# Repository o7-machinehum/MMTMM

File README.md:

# MMM 
Makers Make Music. We're designing and building 100% open source eurorack modules, we would love to hear [from you](https://docs.google.com/forms/d/e/1FAIpQLSeDmKGT8nFPX62po_9shZNs7qYtOch9zK6xhK_ntmRhs4zbUg/viewform?vc=0&c=0&w=1)! All of our designs are done in kicad, which is an open source PCB design software.

## Drum (Bob Bass)
The [Bob Bass](https://github.com/Machine-Hum/MMTMM/tree/master/DrumModule) takes inspiration from the 808 service manual. This guy has knobs all over the place: HPF, LPF, overdrive and control over the resonance and decay. [AUDIO](https://drive.google.com/file/d/1c2VHwUoPN1qcCgDcaHPTnX8EYp0KqyGa/view?usp=sharing) --- [VIDEO](https://www.youtube.com/watch?v=IFoyo2GT42M)

## Logic Crusher
This is a design that conditions synth level audio into 4bit digital. These signals can then be routed through standard TTL logic and then converted back into audio. It's possible to make some very complex sounds. Here is the faceplate, patching is done through the back of the panel.

Some wavforms, the blue is the input and the yellow is the output. <br>

The current setup... (Will be made into a module later)

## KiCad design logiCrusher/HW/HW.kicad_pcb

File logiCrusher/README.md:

# Hardware
## Notes / TODO
- Light pipes in the BOM are too short
- Audio connectors are incorrect (Fixed but double check)
- SWD lines are not correct (Fixed but double check)

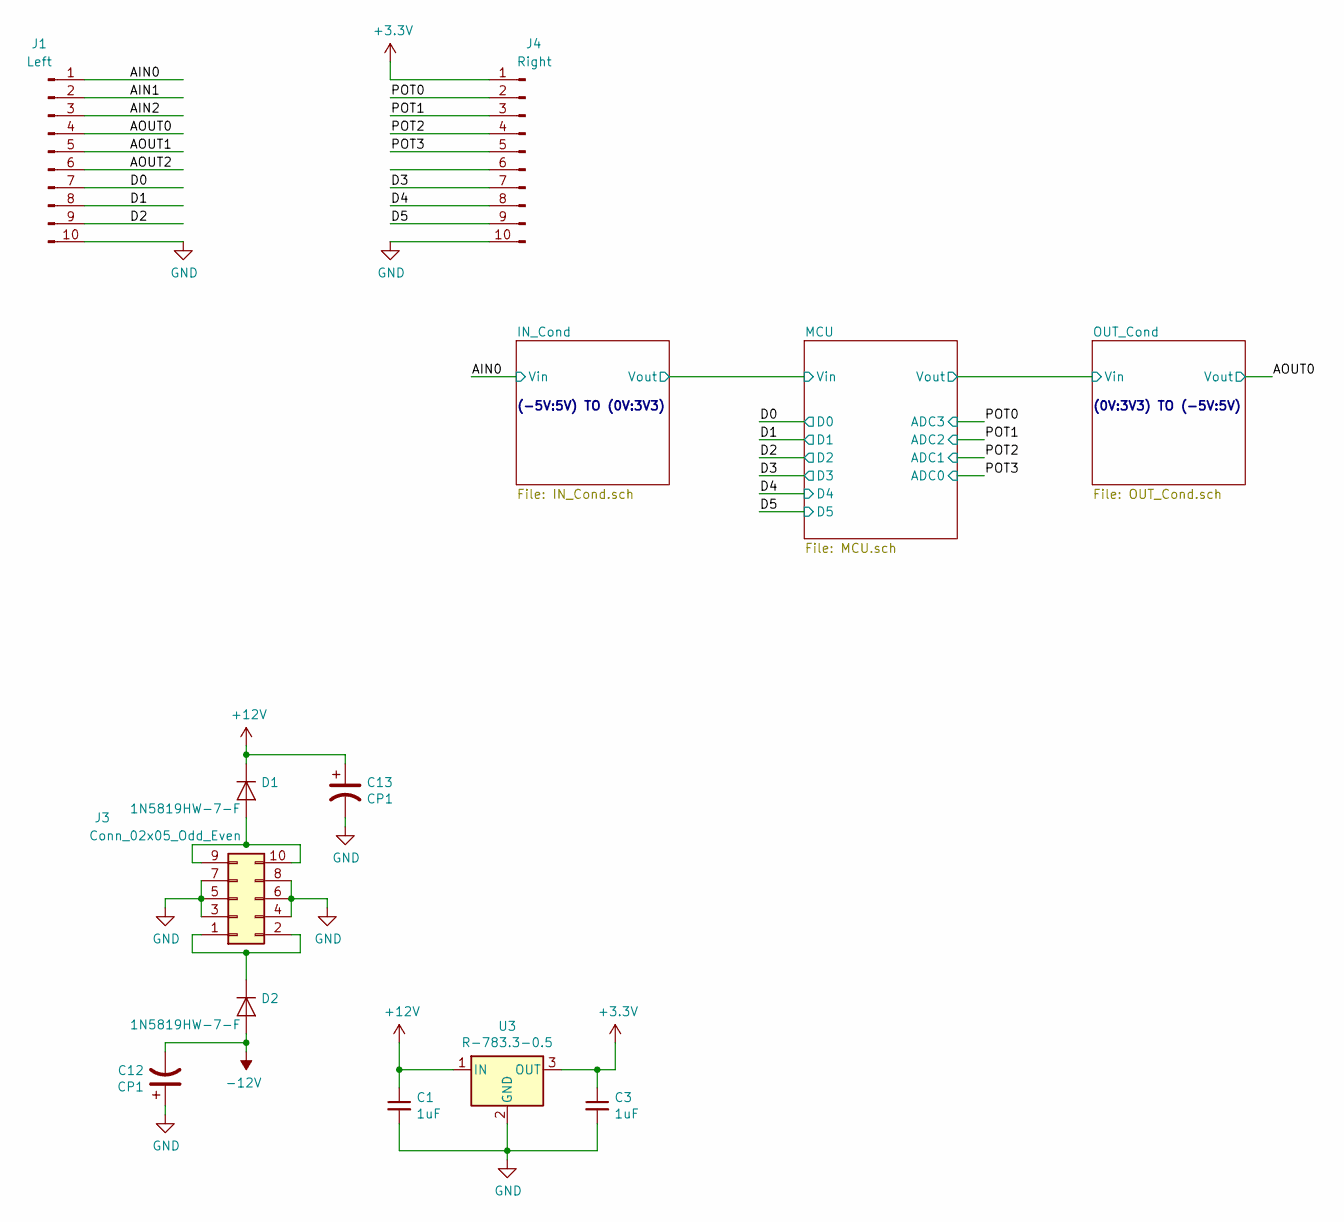
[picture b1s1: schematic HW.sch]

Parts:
C1, C3: 1uF; C_0805_2012Metric
C12, C13: CP1; CP_Elec_3x5.3
D1, D2: 1N5819HW-7-F; D_SOD-123
J1: Left; PinSocket_1x10_P2.54mm_Vertical
J3: Conn_02x05_Odd_Even; IDC-Header_2x05_P2.54mm_Vertical
J4: Right; PinSocket_1x10_P2.54mm_Vertical
U3: R-783.3-0.5; Converter_DCDC_RECOM_R-78E-0.5_THT

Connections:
+3V3: C3.1, J4.1, U3.3 (OUT); also elsewhere on the board
+12V: C1.1, C13.1, D1.1 (K), U3.1 (IN); also elsewhere on the board
-12V: C12.2, D2.2 (A); also elsewhere on the board
/AIN0: J1.1; also elsewhere on the board
/AIN1: J1.2
/AIN2: J1.3
/AOUT0: J1.4; also elsewhere on the board
/AOUT1: J1.5
/AOUT2: J1.6
/D0: J1.7; also elsewhere on the board
/D1: J1.8; also elsewhere on the board
/D2: J1.9; also elsewhere on the board
/D3: J4.7; also elsewhere on the board
/D4: J4.8; also elsewhere on the board
/D5: J4.9; also elsewhere on the board
/POT0: J4.2; also elsewhere on the board
/POT1: J4.3; also elsewhere on the board
/POT2: J4.4; also elsewhere on the board
/POT3: J4.5; also elsewhere on the board
GND: C1.2, C3.2, C12.1, C13.2, J1.10, J3.3, J3.4, J3.5, J3.6, J3.7, J3.8, J4.10, U3.2 (GND); also elsewhere on the board
unnamed: D1.2 (A), J3.9, J3.10
unnamed: D2.1 (K), J3.1, J3.2

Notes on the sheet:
(-5V:5V) TO (0V:3V3)
(0V:3V3) TO (-5V:5V)

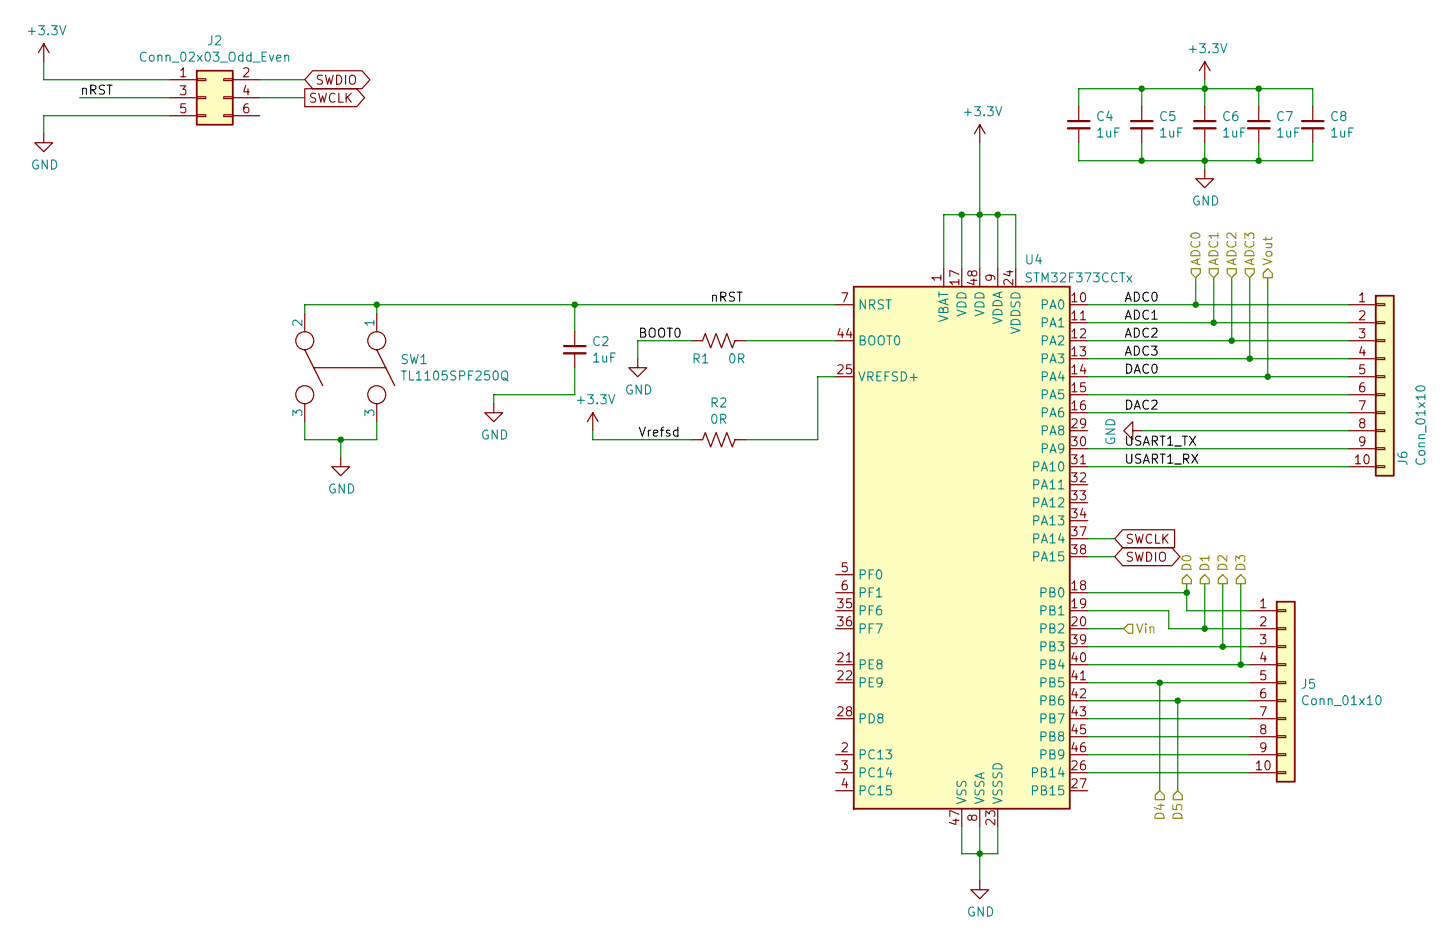
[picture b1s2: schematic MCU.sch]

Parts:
C2, C4, C5, C6, C7, C8: 1uF; C_0805_2012Metric
J2: Conn_02x03_Odd_Even; PinHeader_2x03_P2.54mm_Vertical
J5, J6: Conn_01x10; PinHeader_1x10_P2.54mm_Vertical
R1, R2: 0R; R_0805_2012Metric
SW1: TL1105SPF250Q
U4: STM32F373CCTx; LQFP-48_7x7mm_P0.5mm

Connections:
+3V3: C4.1, C5.1, C6.1, C7.1, C8.1, J2.1, R2.2, U4.1 (VBAT), U4.9 (VDDA), U4.17 (VDD), U4.24 (VDDSD), U4.48 (VDD); also elsewhere on the board
/D0: J5.1, U4.18 (PB0); also elsewhere on the board
/D1: J5.2, U4.19 (PB1); also elsewhere on the board
/D2: J5.3, U4.39 (PB3); also elsewhere on the board
/D3: J5.4, U4.40 (PB4); also elsewhere on the board
/D4: J5.5, U4.41 (PB5); also elsewhere on the board
/D5: J5.6, U4.42 (PB6); also elsewhere on the board
/MCU/DAC2: J6.7, U4.16 (PA6)
/MCU/USART1_RX: J6.10, U4.31 (PA10)
/MCU/USART1_TX: J6.9, U4.30 (PA9)
/MCU/Vin: U4.20 (PB2); also elsewhere on the board
/MCU/nRST: C2.1, J2.3, SW1.1, SW1.2, U4.7 (NRST)
/OUT_Cond/Vin: J6.5, U4.14 (PA4); also elsewhere on the board
/POT0: J6.4, U4.13 (PA3); also elsewhere on the board
/POT1: J6.3, U4.12 (PA2); also elsewhere on the board
/POT2: J6.2, U4.11 (PA1); also elsewhere on the board
/POT3: J6.1, U4.10 (PA0); also elsewhere on the board
GND: C2.2, C4.2, C5.2, C6.2, C7.2, C8.2, J2.5, J6.8, R1.2, SW1.3, U4.8 (VSSA), U4.23 (VSSSD), U4.47 (VSS); also elsewhere on the board
unnamed: J5.7, U4.43 (PB7)
unnamed: J5.8, U4.45 (PB8)
unnamed: J5.9, U4.46 (PB9)
unnamed: J5.10, U4.26 (PB14)
unnamed: J6.6, U4.15 (PA5)
unnamed: R1.1, U4.44 (BOOT0)
unnamed: R2.1, U4.25 (VREFSD+)
SWCLK: J2.4, U4.37 (PA14)
SWDIO: J2.2, U4.38 (PA15)

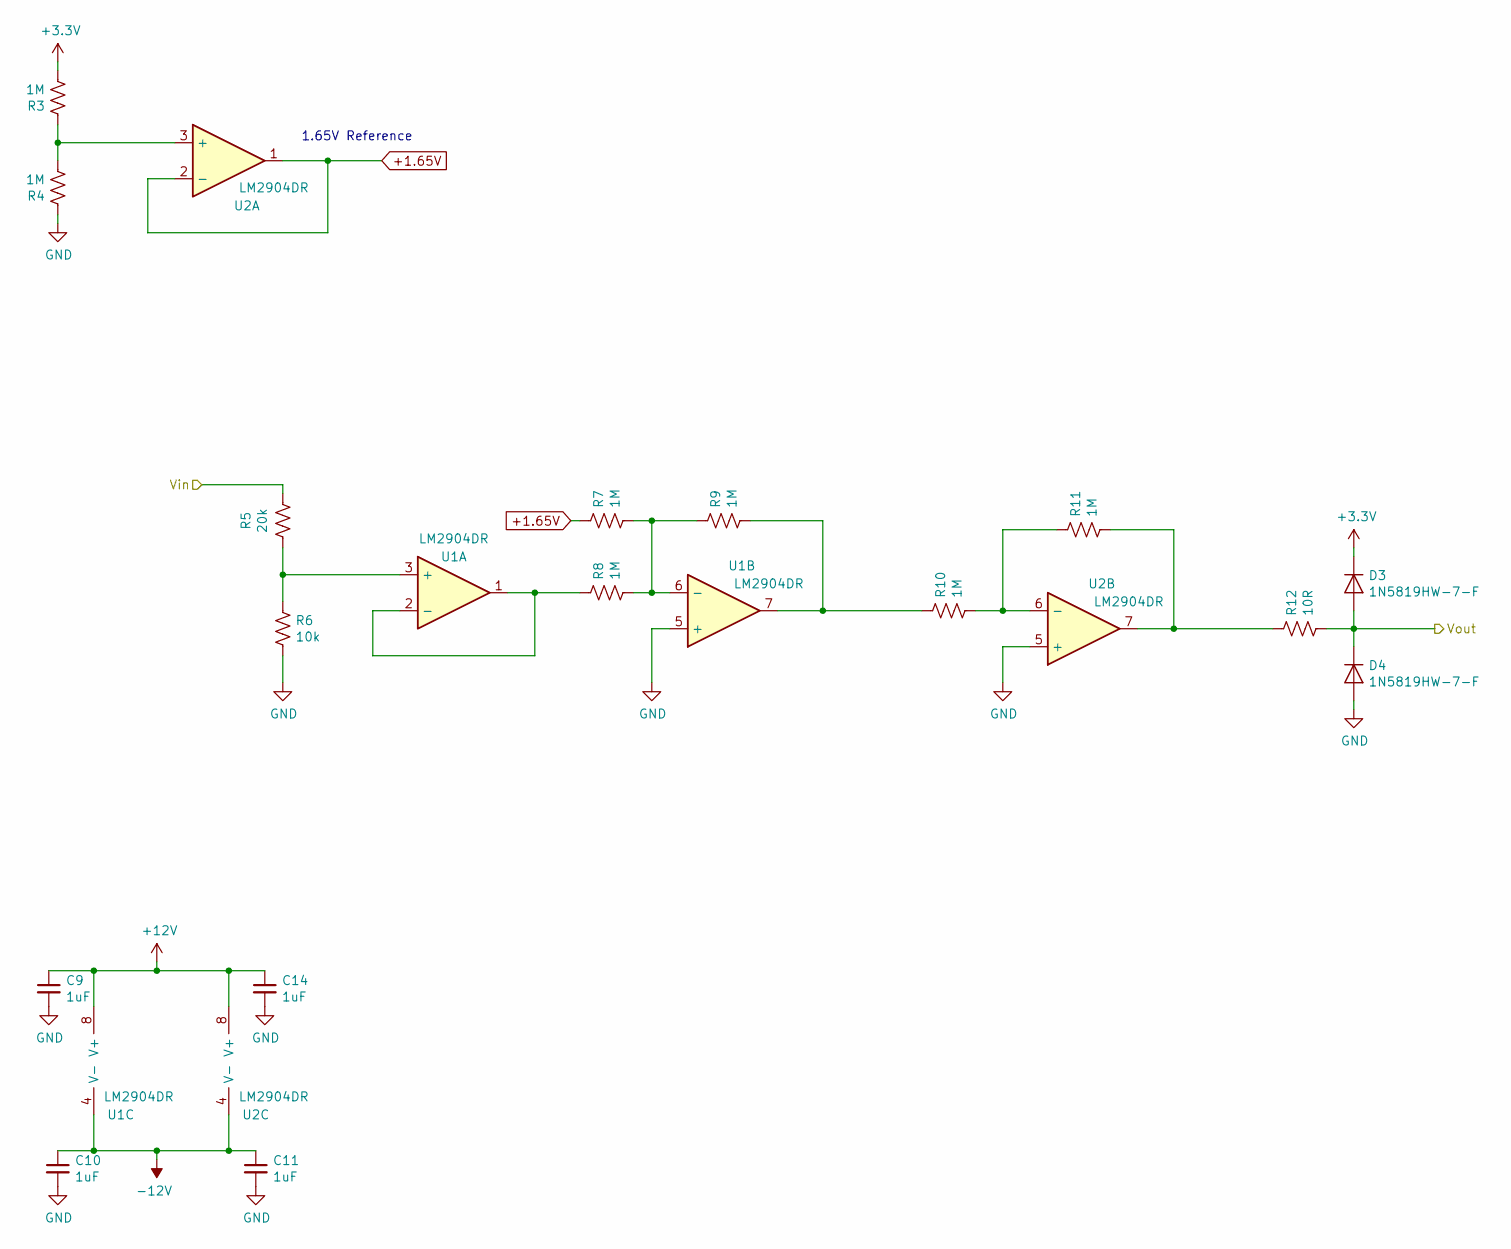
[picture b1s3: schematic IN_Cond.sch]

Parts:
C9, C10, C11, C14: 1uF; C_0805_2012Metric
D3, D4: 1N5819HW-7-F; D_SOD-123
R3, R4, R7, R8, R9, R10, R11: 1M; R_0805_2012Metric
R5: 20k; R_0805_2012Metric
R6: 10k; R_0805_2012Metric
R12: 10R; R_0805_2012Metric
U1, U2: LM2904DR; SOIC-8_3.9x4.9mm_P1.27mm

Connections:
+1.65V: R7.2, U2.1, U2.2 (-); also elsewhere on the board
+3V3: D3.1 (K), R3.1; also elsewhere on the board
+12V: C9.1, C14.1, U1.8 (V+), U2.8 (V+); also elsewhere on the board
-12V: C10.1, C11.1, U1.4 (V-), U2.4 (V-); also elsewhere on the board
/AIN0: R5.1; also elsewhere on the board
/MCU/Vin: D3.2 (A), D4.1 (K), R12.1; also elsewhere on the board
GND: C9.2, C10.2, C11.2, C14.2, D4.2 (A), R4.2, R6.1, U1.5 (+), U2.5 (+); also elsewhere on the board
unnamed: R3.2, R4.1, U2.3 (+)
unnamed: R5.2, R6.2, U1.3 (+)
unnamed: R7.1, R8.1, R9.2, U1.6 (-)
unnamed: R8.2, U1.1, U1.2 (-)
unnamed: R10.1, R11.2, U2.6 (-)
unnamed: R9.1, R10.2, U1.7
unnamed: R11.1, R12.2, U2.7

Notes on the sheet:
1.65V Reference

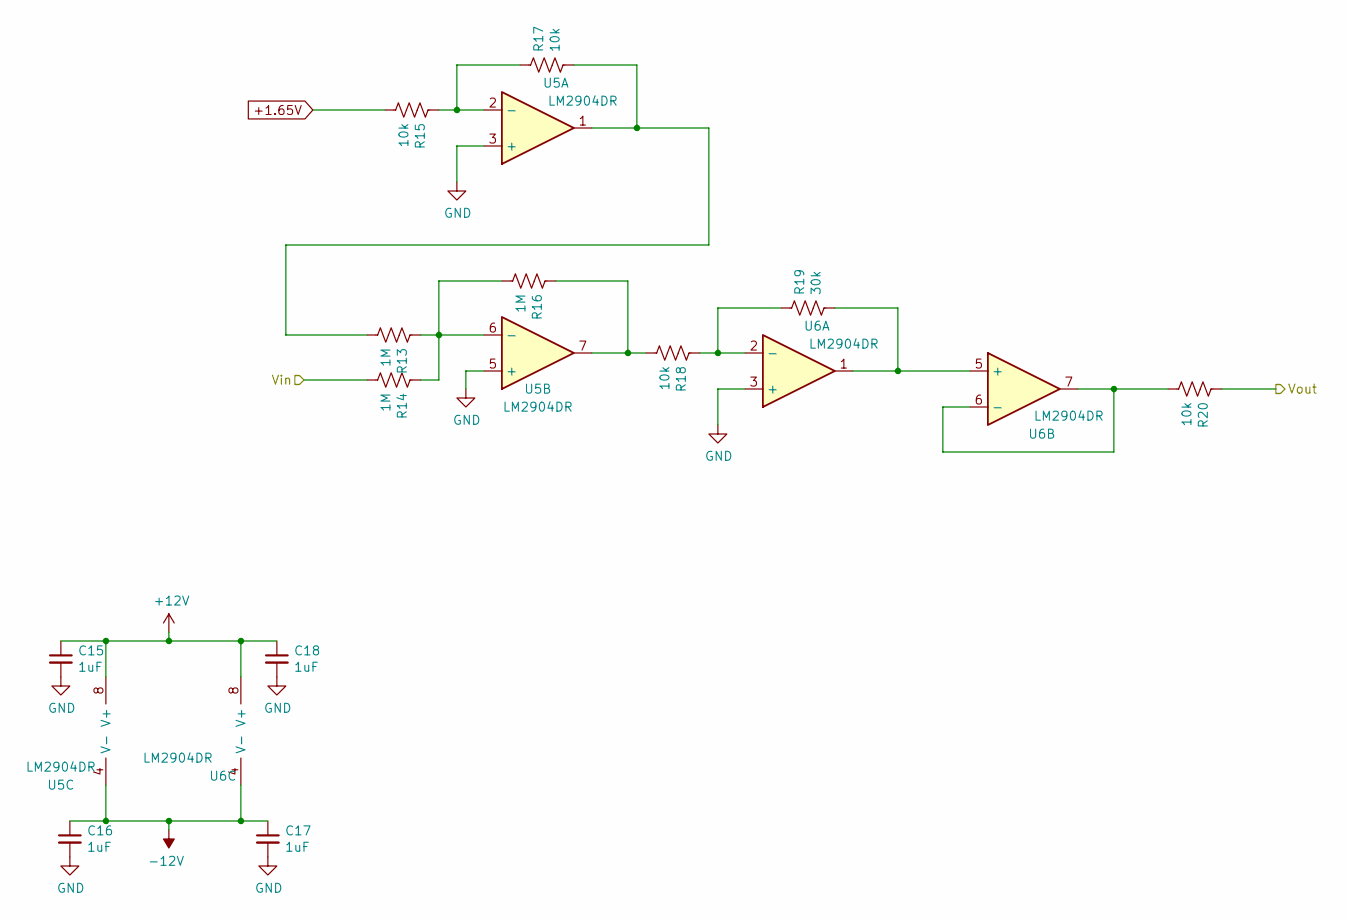
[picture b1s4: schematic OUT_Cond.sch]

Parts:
C15, C16, C17, C18: 1uF; C_0805_2012Metric
R13, R14, R16: 1M; R_0805_2012Metric
R15, R17, R18, R20: 10k; R_0805_2012Metric
R19: 30k; R_0805_2012Metric
U5, U6: LM2904DR; SOIC-8_3.9x4.9mm_P1.27mm

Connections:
+1.65V: R15.1; also elsewhere on the board
+12V: C15.1, C18.1, U5.8 (V+), U6.8 (V+); also elsewhere on the board
-12V: C16.1, C17.1, U5.4 (V-), U6.4 (V-); also elsewhere on the board
/AOUT0: R20.2; also elsewhere on the board
/OUT_Cond/Vin: R14.1; also elsewhere on the board
GND: C15.2, C16.2, C17.2, C18.2, U5.3 (+), U5.5 (+), U6.3 (+); also elsewhere on the board
unnamed: R13.1, R17.1, U5.1
unnamed: R13.2, R14.2, R16.1, U5.6 (-)
unnamed: R15.2, R17.2, U5.2 (-)
unnamed: R16.2, R18.1, U5.7
unnamed: R18.2, R19.2, U6.2 (-)
unnamed: R19.1, U6.1, U6.5 (+)
unnamed: R20.1, U6.6 (-), U6.7

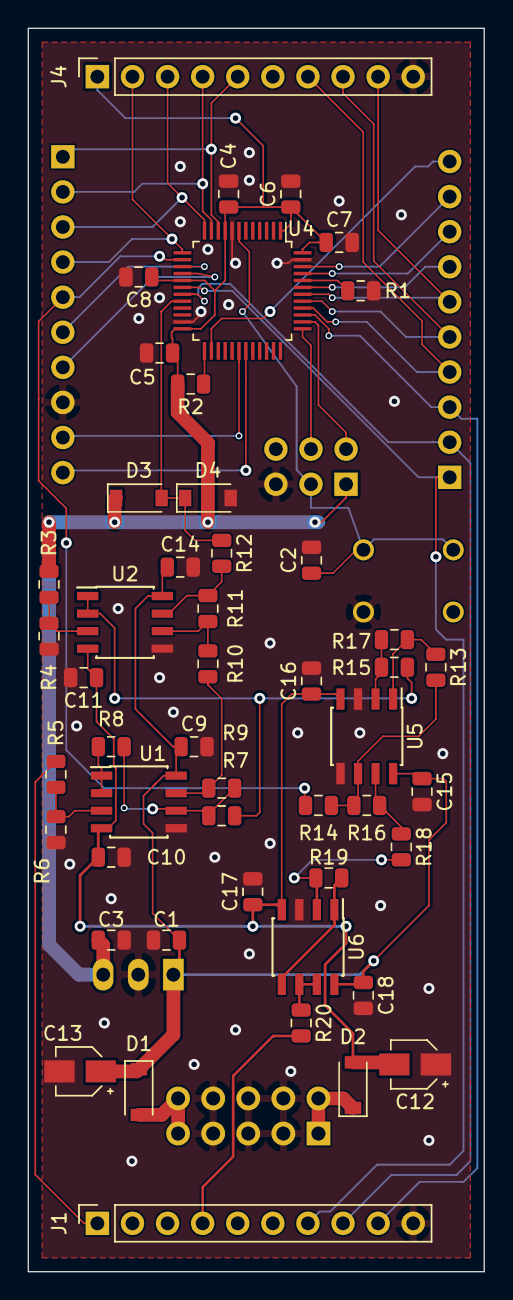
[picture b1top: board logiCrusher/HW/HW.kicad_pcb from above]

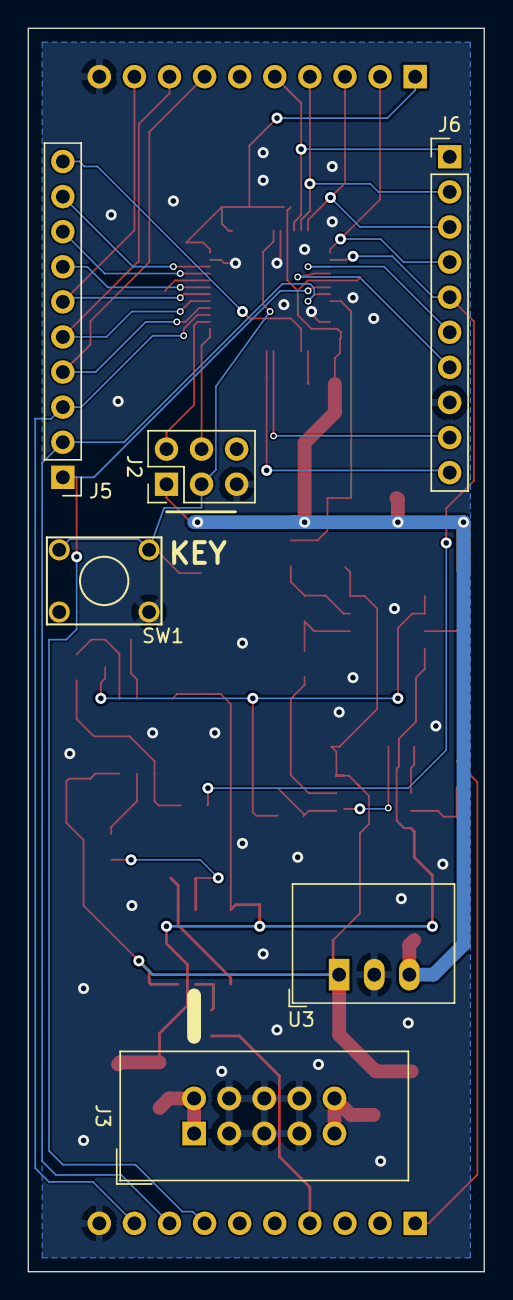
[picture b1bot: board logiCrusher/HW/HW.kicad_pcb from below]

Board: 2 copper layers, 33.0 x 90.0 mm, 55 parts (6 on the bottom side), 48 nets.

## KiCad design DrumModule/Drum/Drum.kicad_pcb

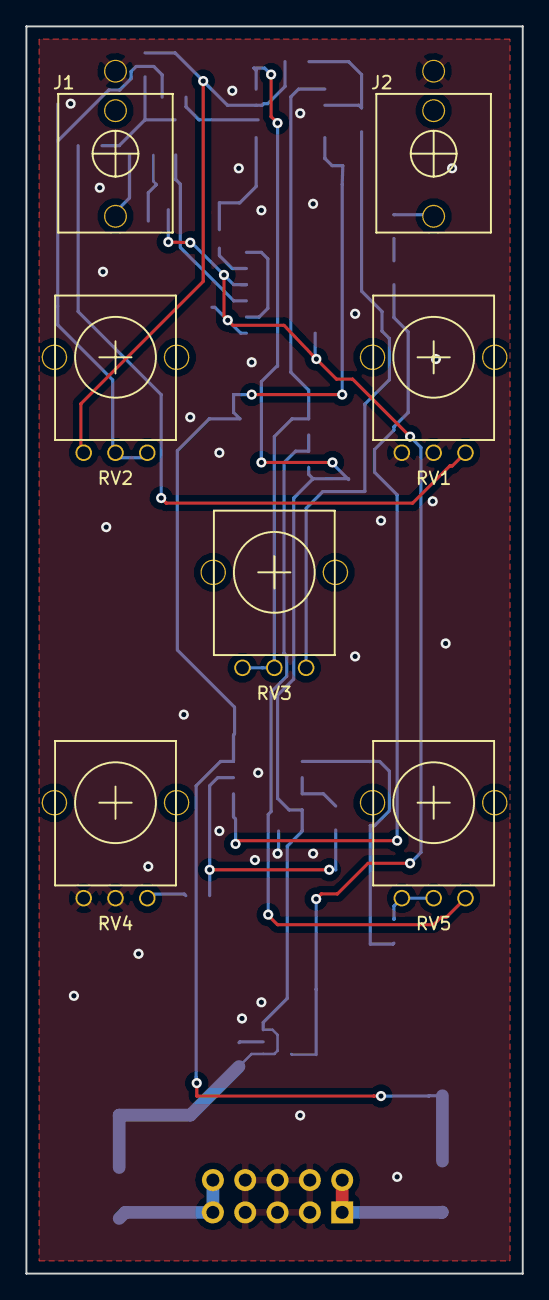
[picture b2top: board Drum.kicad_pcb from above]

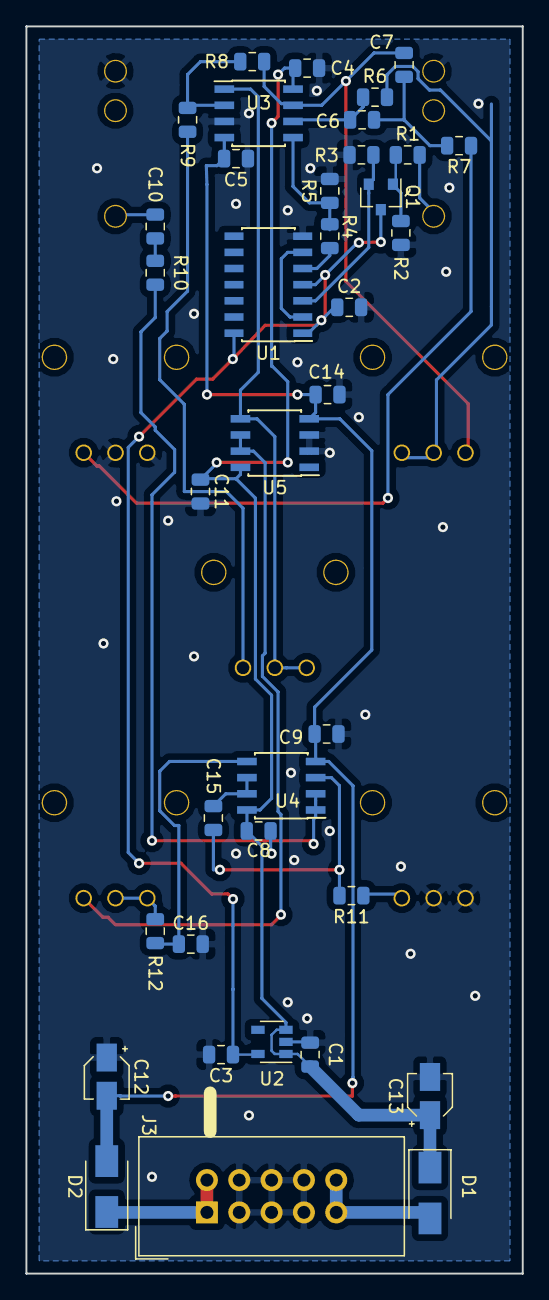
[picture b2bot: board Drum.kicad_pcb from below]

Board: 2 copper layers, 39.0 x 98.0 mm, 44 parts (37 on the bottom side), 29 nets.

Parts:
C1, C2, C3, C4, C5, C8, C9, C10, C11, C14, C15, C16: 1uF; C_0805_2012Metric
C6, C7: 68nF; C_0805_2012Metric
C12, C13: CP1; CP_Elec_3x5.3
D1, D2: STTH102A; D_SMA
J1, J2: Barrel_Jack_Switch; PJ301M-12
J3: Conn_02x05_Odd_Even; IDC-Header_2x05_P2.54mm_Vertical
Q1: MMBT3904; SOT-23
R1: 100k; R_0805_2012Metric
R2, R6: 1M; R_0805_2012Metric
R3, R4, R5, R8, R10, R11, R12: 10k; R_0805_2012Metric
R7: 1k; R_0805_2012Metric
R9: 5k; R_0805_2012Metric
RV1: 5k; Alpha9mmPot
RV2: 1M; Alpha9mmPot
RV3, RV4, RV5: 50k; Alpha9mmPot
U1: 74HC74; SOIC-14_3.9x8.7mm_P1.27mm
U2: MIC5205-5.0YM5; SOT-23-5
U3, U4, U5: LM2904DR; SOIC-8_3.9x4.9mm_P1.27mm

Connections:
+5V: C2.1, C3.1, Q1.3, U1.1, U1.4, U1.14, U2.5
+12V: C1.1, C4.1, C8.1, C11.1, C13.1, D1.1, U2.1, U2.3, U3.8, U4.8, U5.8
-12V: C5.2, C9.2, C12.2, C14.2, D2.2, U3.4, U4.4, U5.4
GND: C1.2, C2.2, C3.2, C4.2, C5.1, C8.2, C9.1, C11.2, C12.1, C13.2, C14.1, C16.2, J1.1, J2.1, J3.3, J3.4, J3.5, J3.6, J3.7, J3.8, R2.2, R3.1, R5.2, RV1.1, RV1.2, RV4.1, RV4.2, U1.7, U2.2, U3.3, U5.2, U5.3
unnamed: C6.1, C7.2, R7.2
unnamed: C6.2, R6.1, U3.6
unnamed: C7.1, R8.1, RV2.1, U3.7
unnamed: C10.1, R10.2
unnamed: C10.2, J2.3
unnamed: C15.1, U4.6, U4.7
unnamed: C15.2, R11.2, U4.3
unnamed: C16.1, R12.2, U4.5
unnamed: D1.2, J3.9, J3.10
unnamed: D2.1, J3.1, J3.2
unnamed: J1.3, R1.2
unnamed: Q1.1, R1.1, R2.1
unnamed: Q1.2, R3.2, U1.3
unnamed: R4.1, U1.5
unnamed: R4.2, R5.1, U3.5
unnamed: R6.2, RV2.2, RV2.3
unnamed: R7.1, RV1.3
unnamed: R8.2, R9.1, U3.2
unnamed: R9.2, RV3.3
unnamed: R10.1, U4.1, U4.2
unnamed: R11.1, RV4.3
unnamed: R12.1, RV5.1, RV5.2
unnamed: RV3.1, RV3.2, U3.1, U5.5
unnamed: RV5.3, U5.6, U5.7
unnamed: U1.2, U1.6

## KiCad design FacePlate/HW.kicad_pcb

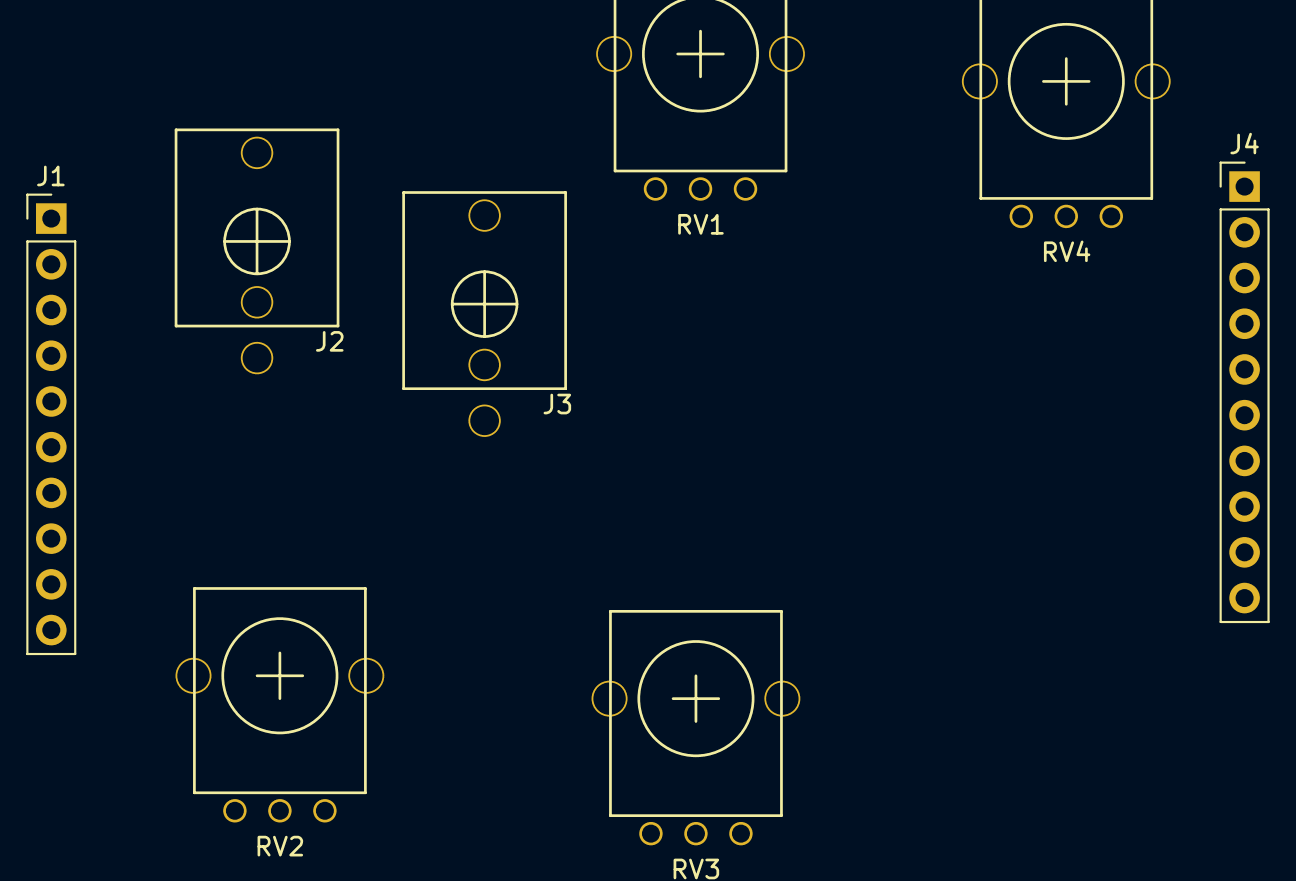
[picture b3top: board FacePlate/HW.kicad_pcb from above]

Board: 2 copper layers, 8 parts (0 on the bottom side), 8 nets, no tracks yet.

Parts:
J1: Left; PinHeader_1x10_P2.54mm_Vertical
J2: Audio In; PJ301M-12
J3: Audio Out; PJ301M-12
J4: Right; PinHeader_1x10_P2.54mm_Vertical
RV1, RV2, RV3, RV4: R_POT_US; Alpha9mmPot

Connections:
+3V3: J4.1, RV1.1, RV2.1, RV3.1, RV4.1
/AIN0: J1.1, J2.2
/AOUT0: J1.4, J3.2
/POT0: J4.2, RV1.2
/POT1: J4.3, RV2.2
/POT2: J4.4, RV3.2
/POT3: J4.5, RV4.2
GND: J1.10, J2.1, J3.1, J4.10, RV1.3, RV2.3, RV3.3, RV4.3

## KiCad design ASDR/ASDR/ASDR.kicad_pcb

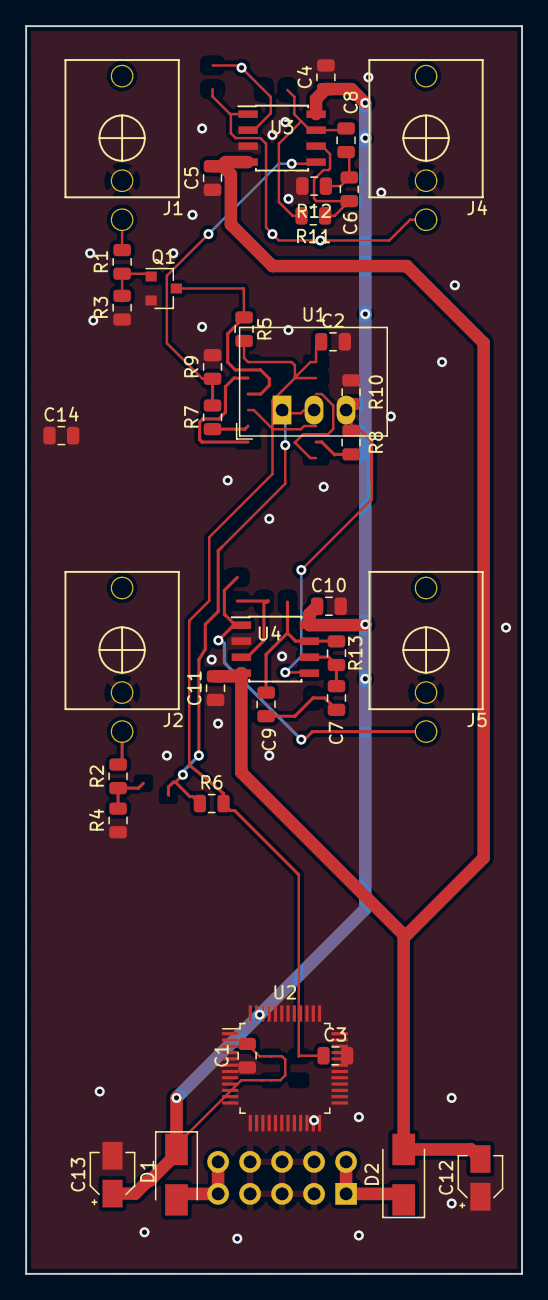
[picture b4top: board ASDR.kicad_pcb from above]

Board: 2 copper layers, 39.4 x 99.1 mm, 39 parts (1 on the bottom side), 26 nets.

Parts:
C1, C2, C3, C4, C5, C6, C7, C8, C9, C10, C11, C14: 1uF; C_0805_2012Metric
C12, C13: CP1; CP_Elec_3x5.3
D1, D2: STTH102A; D_SMA
J1, J4: Barrel_Jack_Switch; PJ301M-12
J2, J5: Conn_01x10; PJ301M-12
J3: Conn_02x05_Odd_Even; IDC-Header_2x05_P2.54mm_Vertical
Q1: MMBT3904; SOT-23
R1, R9: 100k; R_0805_2012Metric
R2, R3, R4, R6, R7, R8, R10, R12: 1M; R_0805_2012Metric
R5: 10k; R_0805_2012Metric
R11: 600k; R_0805_2012Metric
R13: 0R; R_0805_2012Metric
U1: R-783.3-0.5; Converter_DCDC_RECOM_R-78E-0.5_THT
U2: STM32F373CCTx; LQFP-48_7x7mm_P0.5mm
U3, U4: LM2904DR; SOIC-8_3.9x4.9mm_P1.27mm

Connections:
+3V3: C3.1, C4.1, C5.1, C6.1, C7.1, C8.1, R5.2, R6.2, U1.3, U2.1, U2.9, U2.17, U2.24, U2.48
+12V: C1.1, C9.1, C13.1, C14.1, D1.1, U1.1, U3.8, U4.8
-12V: C10.1, C11.1, C12.2, D2.2, U3.4, U4.4
/1.65V: R10.1, U3.6, U3.7
/-1.65V: R4.1, R12.2, U3.1
/ADC0: J2.1, U2.10
/ADC1: J2.2, U2.11
/ADC2: J2.3, U2.12
/nRST: C2.1, U2.7
DAC_OUT: R13.1, U2.14
GND: C1.2, C2.2, C3.2, C4.2, C5.2, C6.2, C7.2, C8.2, C9.2, C10.2, C11.2, C12.1, C13.2, C14.2, J1.2, J3.3, J3.4, J3.5, J3.6, J3.7, J3.8, J4.2, Q1.2, R3.1, R7.1, U1.2, U2.8, U2.23, U2.47, U3.3, U4.3, U4.5
unnamed: D1.2, J3.9, J3.10
unnamed: D2.1, J3.1, J3.2
unnamed: J1.1, R1.2
unnamed: J4.1, R11.1, U4.1
unnamed: J5.1, U2.39
unnamed: J5.2, U2.40
unnamed: J5.3, U2.41
unnamed: Q1.1, R1.1, R3.2
unnamed: R2.2, R4.2, R8.1, U4.6
unnamed: R6.1, R7.2, U3.5
unnamed: R8.2, R9.1, U4.7
unnamed: R10.2, R12.1, U3.2
unnamed: R9.2, R11.2, U4.2
unnamed: R2.1, R13.2
TRIG: Q1.3, R5.1, U2.18

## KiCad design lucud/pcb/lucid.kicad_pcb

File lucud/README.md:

# MMTMM

It's lit.

# Open-VCM ( Very Configurable Module )
The purpose of Open-VCM is to create a low cost platform that's highly configurable. There are three sub-modules that go into the entire module. User can switch them out independently to make entirely different modules.

## Things to think about
- Maybe add LEDs to the spec rather than just digital out
  - TLC59281
- Maybe use 1mm pitch headers rather than 2.54mm

## Requirements
- Affordable
- Ease of use
- Highly modular
- Completely open source
- One module can serve multiple purposes
- Gate: 0V - OFF, 5V - ON. Will be able to handle +-12V.
- CV: +-5V. Will be able to handle +-12V.

## Architecture
There are three main sub-modules that can be mixed and matched with each other.

<div style="text-align:center"></div>

1. Compute, this contains anything that does any signal manipulation. This can be an Arduino, STM32 or analog circuitry.
2. Interface-IO, this is anything that the user interacts with, be it knobs, buttons, jacks etc... The Compute PCB connects with the Interface-IO pcb using a backplane connector.
3. Descriptor, this is the front module that bolts to the Interface-IO PCB. It is only mechanically connected and serves to outline what the knobs, jacks and buttons actually do.

## Backplace connector Signals
- Power ( 6x )
  - 3v3, 5v, +12V, -12V, GND, GND
- Outputs ( 16x )
  - O.0:15
- Inputs ( 16x )
  - I.0:15
- Buttons ( 4x )
  - B.0:3
  - Just pull to GND
- LEDs ( 8x )
  - D.0:7
- SWD ( 3x )
- UART ( 2x )
- USB ( 2x )
- Bootload PB ( 1x )
- nRESET ( 1x )

## Signal Description
The compute PCB is responsible for conditioning all signal to a reasonable level. This is done so the compute PCB can be swapped out for a pure analog PCB in the event the user might wish to build an analog module. All inputs to the compute PCB can handle a full +-12V swing. All outputs are standardised such that they will interface with "normal" eurorack modules.

- Power 
  - As outlined. Shrouded power header on compute PCB. 
- Output
  - +-10V from compute PCB.
- Input
  - +-10V coming from IO pcb.

## MVM ( Minimum viable module )
This is an example of a very low cost configuration that has the highest flexibility. A user could build 5+ of these and change the firmware on each module resulting in a 5 completely different modules.

- IO Module
  - 4x Output Jacks: JO.0:3
    - Lined at the top, apposing JI jacks.
  - 8x Input Jacks: JI.0:7
    - In parallel with static offset pots 
    - 4x lined on the top, while four are elsewhere.
  - 4x Buttons
    - B0:3
  - Reset Button
    - B4
  - Headers for USB / SWD

- Compute Module (Arduino / STM32)
  - 4x ADC
    - I.0:3 - JI.0:3
  - 4x DAC
    - O.0:3 -> JO.0:3
  - GPIO Input
    - I.4:8 -> JI.4:8
  - GPIO Output
    - O.4:8 -> J0.4:8
  - Buttons
    - PB0:PB3 -> B0:3

- Applications
  - VCO
  - VCF
  - Sequencer
  - VCA
  - Divider
  - Sampler
  - ASDR

### Parts
- LM324ADR: Opamp
- 74LVC125AS14-13: Buffer
- STM32F373CCT6: This is a nice part
  - STM32F373VCT6
- R-78E3.3-0.5: Power Supply.

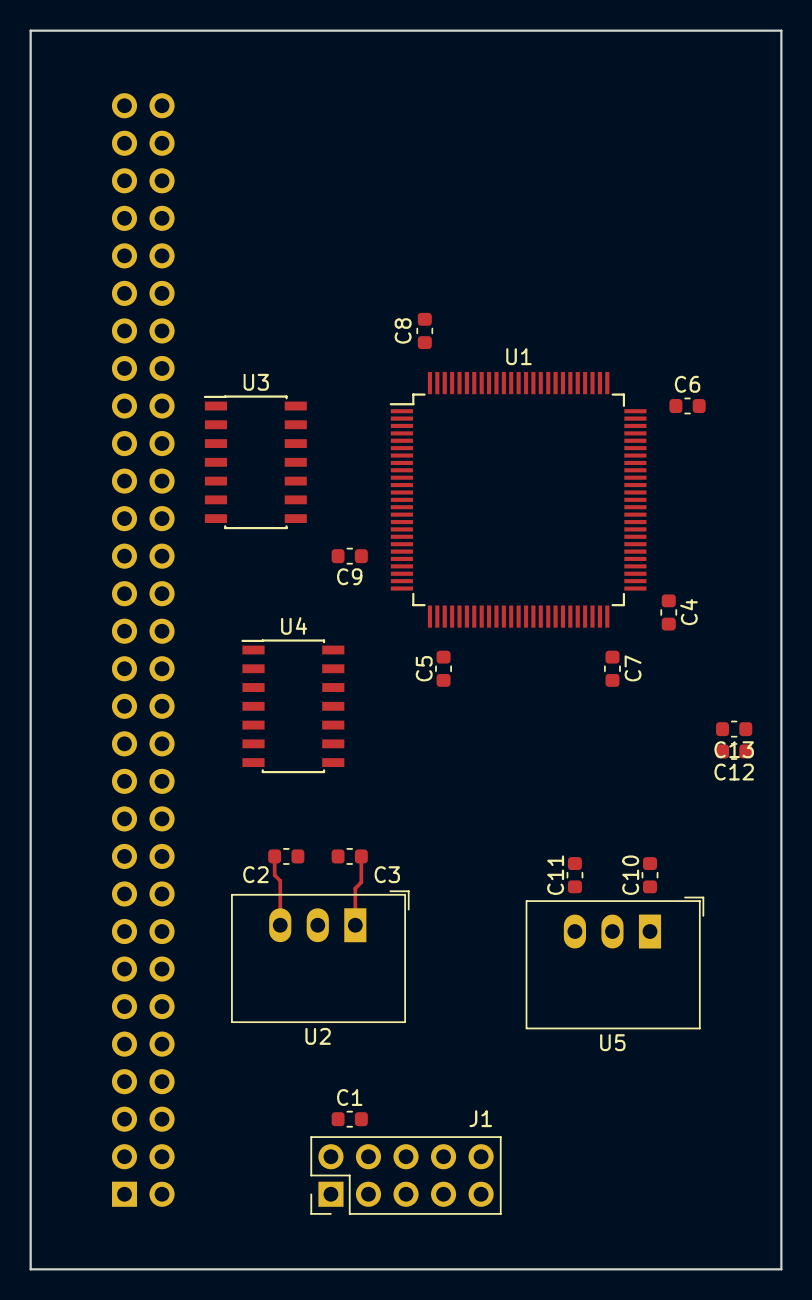
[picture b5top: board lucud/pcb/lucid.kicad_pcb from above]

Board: 4 copper layers, 50.8 x 83.8 mm, 20 parts (1 on the bottom side), 16 nets.

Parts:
C1, C3, C10: 1uF 25V; C_0603_1608Metric
C2, C4, C5, C6, C7, C8, C9, C11, C12, C13: 1uF 6.3V; C_0603_1608Metric
J1: Conn_02x05_Odd_Even; PinHeader_2x05_P2.54mm_Vertical
J2: Conn_02x30_Odd_Even; PinHeader_2x30_P2.54mm_Vertical
U1: STM32F373VCTx; LQFP-100_14x14mm_P0.5mm
U2: R-78E3.3-0.5; Converter_DCDC_RECOM_R-78E-0.5_THT
U3, U4: 74LVC125; SOIC-14_3.9x8.7mm_P1.27mm
U5: R-78E5.0-0.5; Converter_DCDC_RECOM_R-78E-0.5_THT

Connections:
+3V3: C2.1, C4.1, C5.1, C6.1, C7.1, C8.1, C9.1, J2.1, U1.6, U1.21, U1.28, U1.50, U1.51, U1.75, U1.100, U2.3
+5V: C11.1, C12.1, C13.1, U3.1, U3.4, U3.10, U3.13, U3.14, U4.1, U4.4, U4.10, U4.13, U4.14, U5.3
+12V: C1.1, C3.1, C10.1, J1.1, J1.2, J2.3, U2.1, U5.1
-12V: J1.9, J1.10, J2.5
/O.1: J2.9, U3.3
/O.2: J2.11, U3.6
/O.3: J2.13, U3.8
/O.4: J2.15, U3.11
/O.5: J2.17, U4.3
/O.6: J2.19, U4.6
/O.7: J2.21, U4.8
/O.8: J2.23, U4.11
/SWD_CLK: J2.58, U1.72
/SWD_DAT: J2.56, U1.76
/nRST: J2.60, U1.14
GND: C1.2, C2.2, C3.2, C4.2, C5.2, C6.2, C7.2, C8.2, C9.2, C10.2, C11.2, C12.2, C13.2, J1.3, J1.4, J1.5, J1.6, J1.7, J1.8, J2.2, U1.20, U1.49, U1.74, U1.99, U2.2, U3.7, U4.7, U5.2

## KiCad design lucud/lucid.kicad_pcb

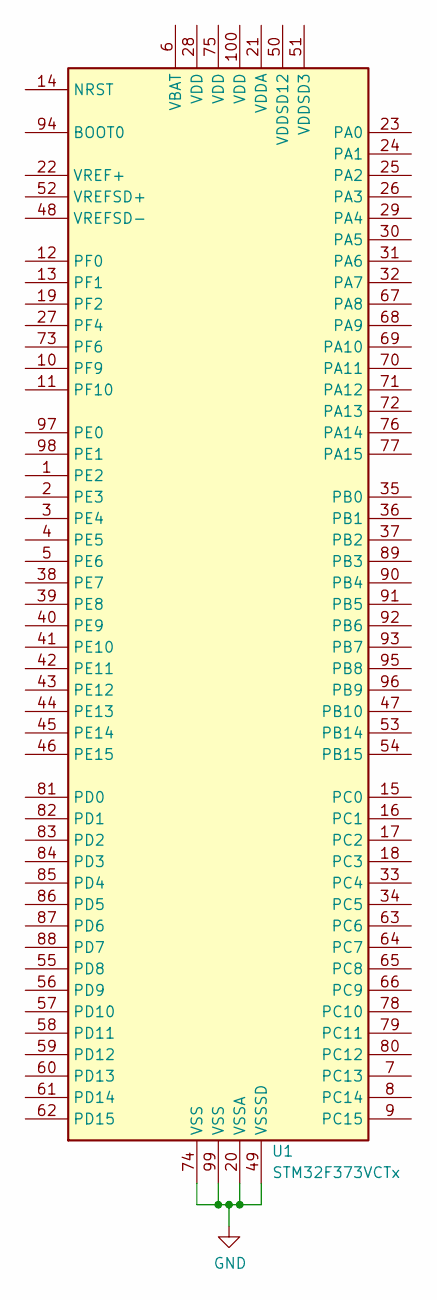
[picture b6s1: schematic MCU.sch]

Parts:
U1: STM32F373VCTx; LQFP-100_14x14mm_P0.5mm

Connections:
GND: U1.20 (VSSA), U1.49 (VSSSD), U1.74 (VSS), U1.99 (VSS); also elsewhere on the board

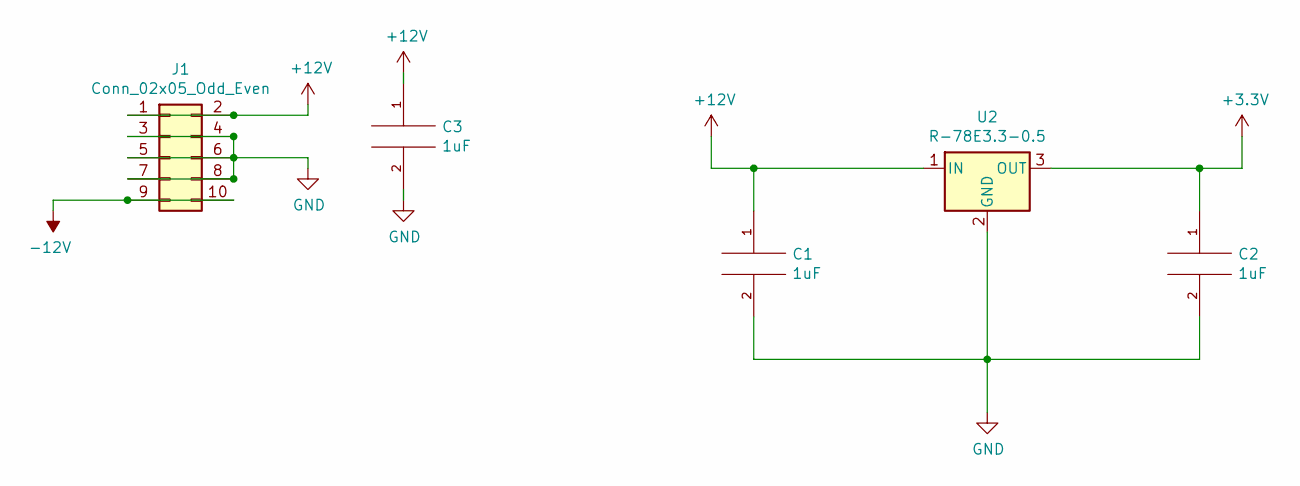
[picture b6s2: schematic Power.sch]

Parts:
C1, C2, C3: 1uF; C_0603_1608Metric
J1: Conn_02x05_Odd_Even; PinHeader_2x05_P2.54mm_Vertical
U2: R-78E3.3-0.5; Converter_DCDC_RECOM_R-78E-0.5_THT

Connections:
+3V3: C2.1, U2.3 (OUT)
+12V: C1.1, C3.1, J1.1, J1.2, U2.1 (IN)
-12V: J1.9, J1.10
GND: C1.2, C2.2, C3.2, J1.3, J1.4, J1.5, J1.6, J1.7, J1.8, U2.2 (GND); also elsewhere on the board

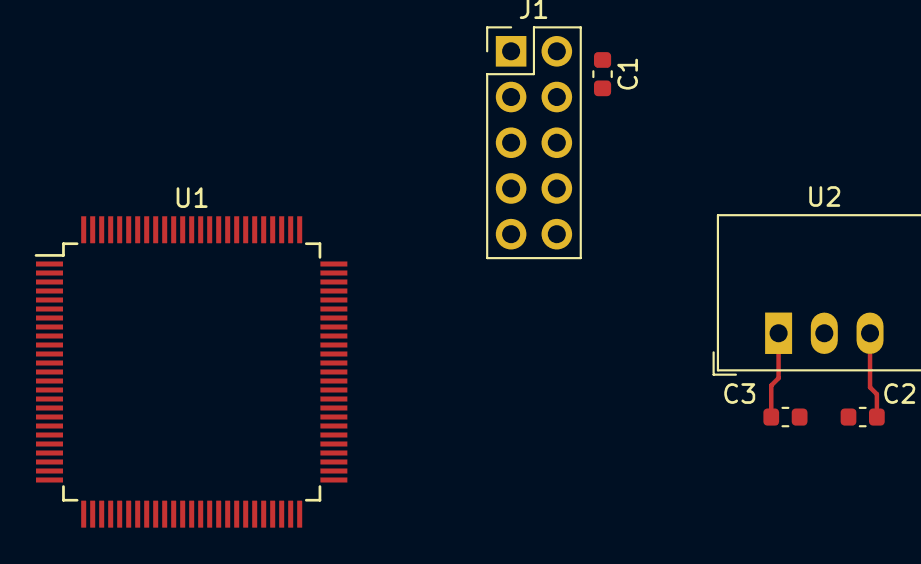
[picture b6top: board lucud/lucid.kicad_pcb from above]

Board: 4 copper layers, 6 parts (0 on the bottom side), 4 nets.
